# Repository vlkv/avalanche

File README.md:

# The Avalanche keyboard

The Avalanche keyboard is an ergonomic split keyboard with 4x6 (or 3x6 if you **break off the 'digits' row**) column staggered keys,
5 thumb keys, **1 additional key for the pinky** (break off-able too) and 2 additional keys for the index finger (64 keys total).

Avalanche design was inspired by a number of great keyboards. You may read more about it
in my very first [reddit post](https://www.reddit.com/r/MechanicalKeyboards/comments/mkwddp/introducing_the_avalanche_yet_another_one_ergo/).

Avalanche v4 (Awesome 40% and 60% builds by [u/chewiedies](https://www.reddit.com/user/chewiedies))

Avalanche v3

Avalanche v2

## Layout tester

Cut [left half](https://github.com/vlkv/avalanche/blob/master/layout_tester/pdf/Avalanche_v3_0_left_A4.pdf) and
[right half](https://github.com/vlkv/avalanche/blob/master/layout_tester/pdf/Avalanche_v3_0_right_A4.pdf)
from some piece of a cardboard, insert switches, put on the keycaps and try the layout.

## Gerber files

* [Version 4.2](https://github.com/vlkv/avalanche/tree/v4.2)
  * [PCB](https://github.com/vlkv/avalanche/blob/v4.2/pcb/Gerbers_pcb_v4_2.zip)
  * [Top plate](https://github.com/vlkv/avalanche/blob/v4.1/plate_top/Gerbers_plate_top_v4_1.zip)
  * [Bottom plate](https://github.com/vlkv/avalanche/blob/v4.1/plate_bottom/Gerbers_plate_bottom_v4_1.zip)
  * [60% 3D printed case](https://www.thingiverse.com/thing:5183389)
  * [40% 3D printed case](https://www.thingiverse.com/thing:5183613)
* [Version 3.1](https://github.com/vlkv/avalanche/tree/v3.1).
  * [PCB](https://github.com/vlkv/avalanche/blob/v3.1/pcb/Gerbers_pcb_v3_1.zip)
  * [Top plate](https://github.com/vlkv/avalanche/blob/v3.1/plate_top/Gerbers_plate_top_v3_0.zip)
  * [Bottom plate](https://github.com/vlkv/avalanche/blob/v3.1/plate_bottom/Gerbers_plate_bottom_v3_0.zip)
  * [Cover](https://github.com/vlkv/avalanche/blob/v3.1/cover/Gerbers_cover_v3_0.zip).
* [Version 3.0](https://github.com/vlkv/avalanche/tree/v3.0).
  * Known issues:
    * Still not fixed! https://github.com/vlkv/avalanche/issues/8
  * [PCB](https://github.com/vlkv/avalanche/blob/v3.0/pcb/Gerbers_pcb_v3_0.zip)
  * [Top plate](https://github.com/vlkv/avalanche/blob/v3.0/plate_top/Gerbers_plate_top_v3_0.zip)
  * [Bottom plate](https://github.com/vlkv/avalanche/blob/v3.0/plate_bottom/Gerbers_plate_bottom_v3_0.zip)
  * [Cover](https://github.com/vlkv/avalanche/blob/master/cover/Gerbers_cover_v3_0.zip). TODO: use git tag in this URI
* [Version 2.2](https://github.com/vlkv/avalanche/tree/v2.2).
  * Known issues:
    * Still not fixed! https://github.com/vlkv/avalanche/issues/8
  * [PCB](https://github.com/vlkv/avalanche/blob/v2.2/pcb/Gerbers_pcb.zip)
  * [Top plate](https://github.com/vlkv/avalanche/blob/v2.2/plate_top/Gerbers_plate_top.zip)
  * [Bottom plate](https://github.com/vlkv/avalanche/blob/v2.2/plate_bottom/Gerbers_plate_bottom.zip)
  * TODO: Add ProMicro/OLED cover gerber files...
* [Version 1.1](https://github.com/vlkv/avalanche/tree/v1.1).
  * [PCB](https://github.com/vlkv/avalanche/blob/v1.1/pcb/Gerbers_pcb.zip)
  * [Top plate](https://github.com/vlkv/avalanche/blob/v1.1/plate_top/Gerbers_plate_top.zip)
  * [Bottom plate](https://github.com/vlkv/avalanche/blob/v1.1/plate_bottom/Gerbers_plate_bottom.zip)

## Release notes
Are [here](https://github.com/vlkv/avalanche/blob/master/release_notes.md).

## Parts list
Is [here](https://github.com/vlkv/avalanche/blob/master/parts_list.md).

## Build instructions

Are [here](https://github.com/vlkv/avalanche/blob/master/build_instructions.md). These instructions are very brief
and insufficient as a detailed build instructions for a beginner. That is why (if you are a beginner) I recommend you
to also read these resourses:
* [ErgoTravel Build Instructions](https://github.com/jpconstantineau/ErgoTravel/blob/master/BuildInstructions.md)
* [Jian Build Instructons](https://telegra.ph/Gajd-po-sborke-Jian-12-08)
* [Joric wiki](https://github.com/joric/jorne/wiki)

## Chat group
There is a [chat group in Telegram](https://t.me/avalanche_kb), where you may chat about the project or ask some questions/help.

## Firmware

* [QMK](https://github.com/vlkv/qmk_firmware/tree/master/keyboards/avalanche).
* [ZMK from our friend romones](https://github.com/romones/zmk-config). According to him: "Keyboard works, encoders work. I couldn’t figure out lights and displays. And if you plan to use it note there is an override for a dead pin in right overlay".

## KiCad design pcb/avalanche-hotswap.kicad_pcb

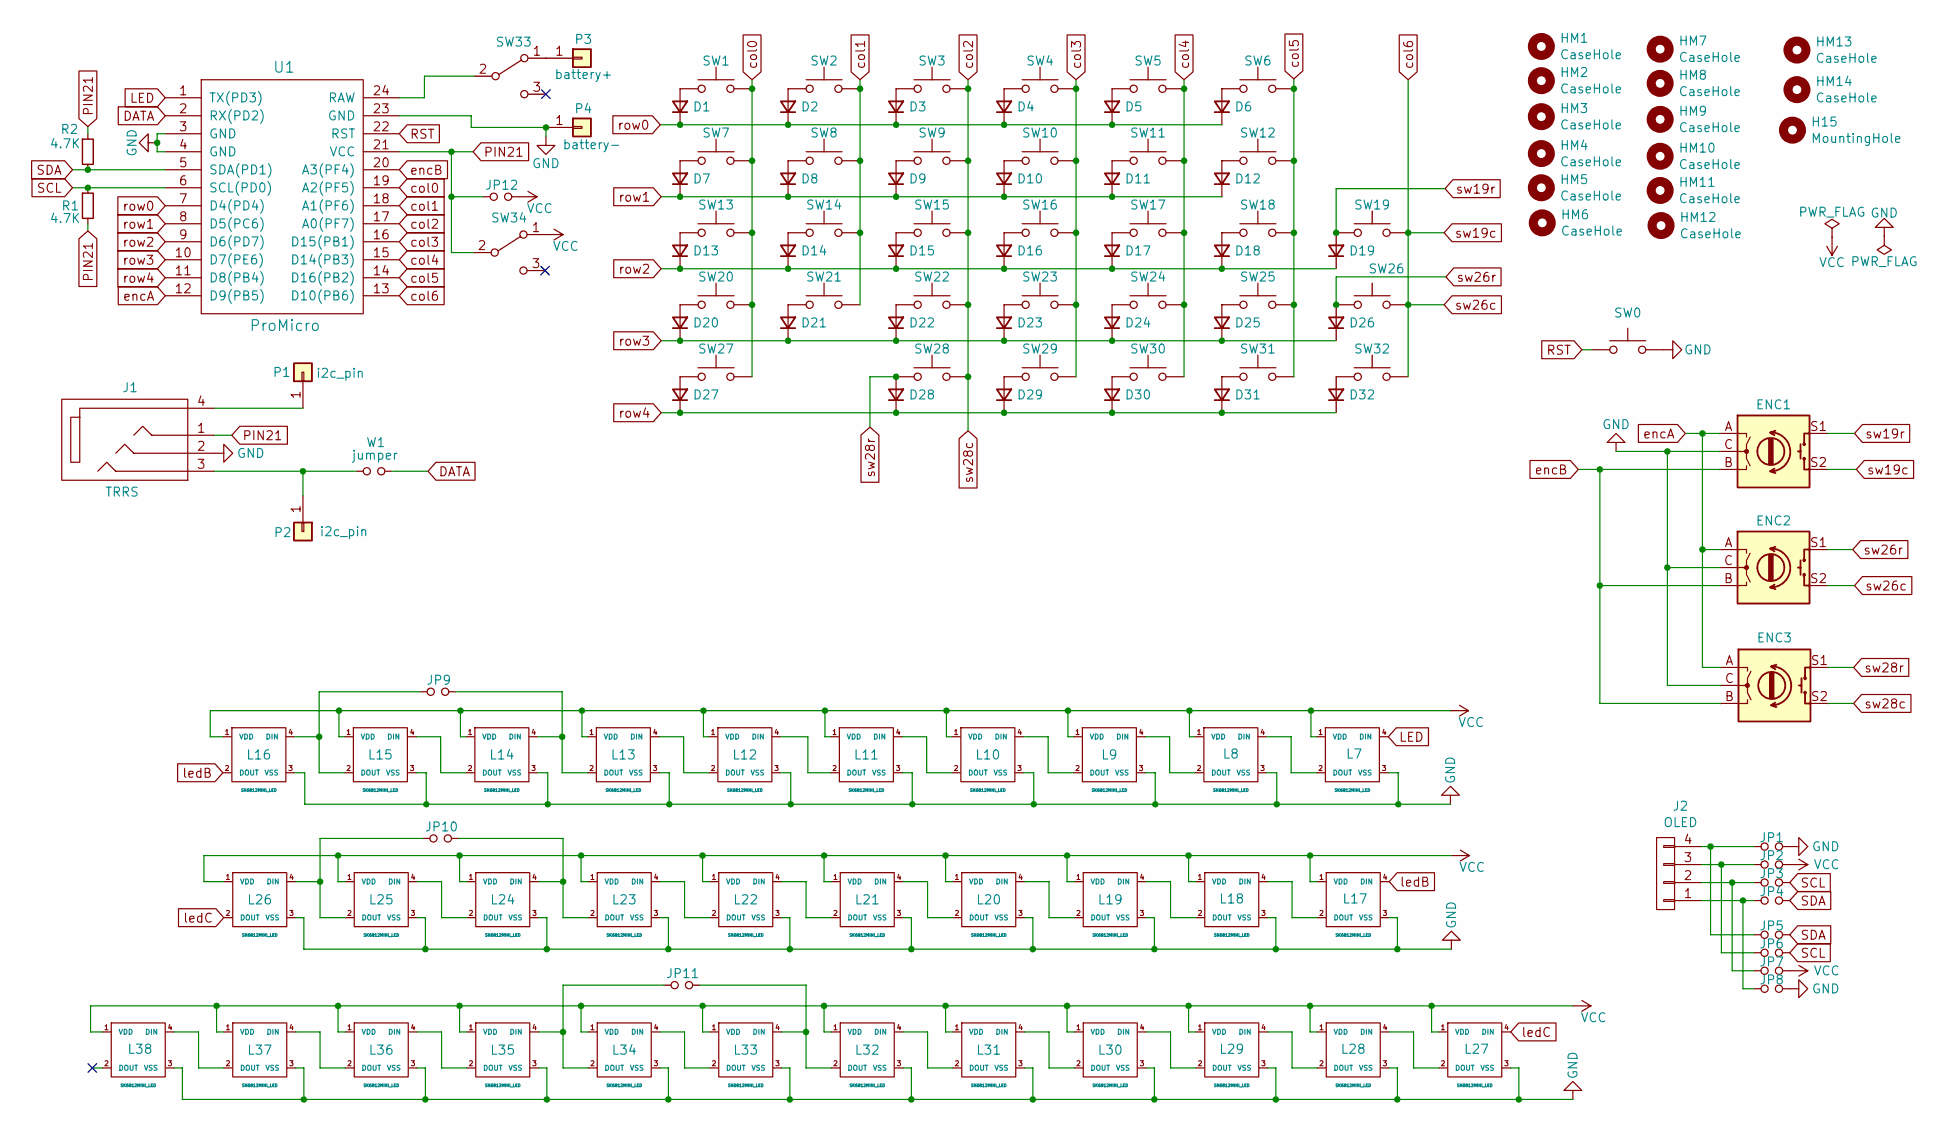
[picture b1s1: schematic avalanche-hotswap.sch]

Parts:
D1, D2, D3, D4, D5, D6, D7, D8, D9, D10, D11, D12, D13, D14, D15, D16, D17, D18, D19, D20, D21, D22, D23, D24, D25, D26, D27, D28, D29, D30, D31, D32: 1N4148; diode_TH_SMD
ENC1, ENC2, ENC3: Rotary_Encoder_Switch; RotaryEncoder_Alps_EC11E-Switch_Vertical_H20mm-keebio_modif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
H15: MountingHole; M2_HOLE_PCB
HM1, HM2, HM3, HM4, HM5, HM6, HM7, HM8, HM9, HM10, HM11, HM12, HM13, HM14: CaseHole; M2_HOLE_PCB
J1: TRRS; MJ-4PP-9
J2: OLED; OLED_4Pin_SSD1306
JP1, JP2, JP3, JP4, JP5, JP6, JP7, JP8, JP12: Device_Jumper_NO_Small; avalanche_Jumper
JP9, JP10, JP11: Device_Jumper_NO_Small; Jumper_rev
L7, L8, L9, L10, L11, L12, L13, L14, L15, L16, L17, L18, L19, L20, L21, L22, L23, L24, L25, L26, L27, L28, L29, L30, L31, L32, L33, L34, L35, L36, L37, L38: SK6812MINI_LED; YS-SK6812MINI-E
P1, P2: i2c_pin; 1pin_conn
P3: battery+; 1pin_conn
P4: battery-; 1pin_conn
R1, R2: 4.7K; Resistor_Hybrid_1205
SW0: SW_Push; Switch_Reset_THT
SW1, SW2, SW3, SW4, SW5, SW6, SW7, SW8, SW9, SW10, SW11, SW12, SW13, SW14, SW15, SW16, SW17, SW18, SW19, SW20, SW21, SW22, SW23, SW24, SW25, SW26, SW27, SW28, SW29, SW30, SW31, SW32: SW_Push; CherryMX_MidHeight_Hotswap_1u
SW33, SW34: SW_DPDT_x2; Switch_MSK-12C01-07
U1: ProMicro; ProMicro_rev2
W1: jumper; avalanche_Jumper

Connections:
DATA: U1.2 (RX(PD2)), W1.1
GND: ENC1.C, ENC2.C, ENC3.C, J1.2, JP1.2, JP8.2, L7.3 (VSS), L8.3 (VSS), L9.3 (VSS), L10.3 (VSS), L11.3 (VSS), L12.3 (VSS), L13.3 (VSS), L14.3 (VSS), L15.3 (VSS), L16.3 (VSS), L17.3 (VSS), L18.3 (VSS), L19.3 (VSS), L20.3 (VSS), L21.3 (VSS), L22.3 (VSS), L23.3 (VSS), L24.3 (VSS), L25.3 (VSS), L26.3 (VSS), L27.3 (VSS), L28.3 (VSS), L29.3 (VSS), L30.3 (VSS), L31.3 (VSS), L32.3 (VSS), L33.3 (VSS), L34.3 (VSS), L35.3 (VSS), L36.3 (VSS), L37.3 (VSS), L38.3 (VSS), P4.1, SW0.2, U1.3 (GND), U1.4 (GND), U1.23 (GND)
LED: L7.4 (DIN), U1.1 (TX(PD3))
unnamed: D1.2 (A), SW1.1
unnamed: D2.2 (A), SW2.1
unnamed: D3.2 (A), SW3.1
unnamed: D4.2 (A), SW4.1
unnamed: D5.2 (A), SW5.1
unnamed: D6.2 (A), SW6.1
unnamed: D7.2 (A), SW7.1
unnamed: D8.2 (A), SW8.1
unnamed: D9.2 (A), SW9.1
unnamed: D10.2 (A), SW10.1
unnamed: D11.2 (A), SW11.1
unnamed: D12.2 (A), SW12.1
unnamed: D13.2 (A), SW13.1
unnamed: D14.2 (A), SW14.1
unnamed: D15.2 (A), SW15.1
unnamed: D16.2 (A), SW16.1
unnamed: D17.2 (A), SW17.1
unnamed: D18.2 (A), SW18.1
unnamed: D20.2 (A), SW20.1
unnamed: D21.2 (A), SW21.1
unnamed: D22.2 (A), SW22.1
unnamed: D23.2 (A), SW23.1
unnamed: D24.2 (A), SW24.1
unnamed: D25.2 (A), SW25.1
unnamed: D27.2 (A), SW27.1
unnamed: D29.2 (A), SW29.1
unnamed: D30.2 (A), SW30.1
unnamed: D31.2 (A), SW31.1
unnamed: D32.2 (A), SW32.1
unnamed: J1.3, P2.1, W1.2
unnamed: J1.4, P1.1
unnamed: J2.1, JP4.1, JP8.1
unnamed: J2.2, JP3.1, JP7.1
unnamed: J2.3, JP2.1, JP6.1
unnamed: J2.4, JP1.1, JP5.1
unnamed: JP9.1, L15.2 (DOUT), L16.4 (DIN)
unnamed: JP9.2, L13.2 (DOUT), L14.4 (DIN)
unnamed: JP10.1, L25.2 (DOUT), L26.4 (DIN)
unnamed: JP10.2, L23.2 (DOUT), L24.4 (DIN)
unnamed: JP11.1, L34.2 (DOUT), L35.4 (DIN)
unnamed: JP11.2, L32.2 (DOUT), L33.4 (DIN)
unnamed: L7.2 (DOUT), L8.4 (DIN)
unnamed: L8.2 (DOUT), L9.4 (DIN)
unnamed: L10.2 (DOUT), L11.4 (DIN)
unnamed: L9.2 (DOUT), L10.4 (DIN)
unnamed: L11.2 (DOUT), L12.4 (DIN)
unnamed: L12.2 (DOUT), L13.4 (DIN)
unnamed: L14.2 (DOUT), L15.4 (DIN)
unnamed: L17.2 (DOUT), L18.4 (DIN)
unnamed: L18.2 (DOUT), L19.4 (DIN)
unnamed: L19.2 (DOUT), L20.4 (DIN)
unnamed: L20.2 (DOUT), L21.4 (DIN)
unnamed: L21.2 (DOUT), L22.4 (DIN)
unnamed: L22.2 (DOUT), L23.4 (DIN)
unnamed: L24.2 (DOUT), L25.4 (DIN)
unnamed: L27.2 (DOUT), L28.4 (DIN)
unnamed: L28.2 (DOUT), L29.4 (DIN)
unnamed: L29.2 (DOUT), L30.4 (DIN)
unnamed: L30.2 (DOUT), L31.4 (DIN)
unnamed: L31.2 (DOUT), L32.4 (DIN)
unnamed: L33.2 (DOUT), L34.4 (DIN)
unnamed: L35.2 (DOUT), L36.4 (DIN)
unnamed: L36.2 (DOUT), L37.4 (DIN)
unnamed: L37.2 (DOUT), L38.4 (DIN)
unnamed: P3.1, SW33.1 (A)
unnamed: SW33.2 (B), U1.24 (RAW)
PIN21: J1.1, JP12.1, R1.2, R2.1, SW34.2 (B), U1.21 (VCC)
RST: SW0.1, U1.22 (RST)
SCL: JP3.2, JP6.2, R1.1, U1.6 (SCL(PD0))
SDA: JP4.2, JP5.2, R2.2, U1.5 (SDA(PD1))
VCC: JP2.2, JP7.2, JP12.2, L7.1 (VDD), L8.1 (VDD), L9.1 (VDD), L10.1 (VDD), L11.1 (VDD), L12.1 (VDD), L13.1 (VDD), L14.1 (VDD), L15.1 (VDD), L16.1 (VDD), L17.1 (VDD), L18.1 (VDD), L19.1 (VDD), L20.1 (VDD), L21.1 (VDD), L22.1 (VDD), L23.1 (VDD), L24.1 (VDD), L25.1 (VDD), L26.1 (VDD), L27.1 (VDD), L28.1 (VDD), L29.1 (VDD), L30.1 (VDD), L31.1 (VDD), L32.1 (VDD), L33.1 (VDD), L34.1 (VDD), L35.1 (VDD), L36.1 (VDD), L37.1 (VDD), L38.1 (VDD), SW34.1 (A)
col0: SW1.2, SW7.2, SW13.2, SW20.2, SW27.2, U1.19 (A2(PF5))
col1: SW2.2, SW8.2, SW14.2, SW21.2, U1.18 (A1(PF6))
col2: ENC3.S2, SW3.2, SW9.2, SW15.2, SW22.2, SW28.2, U1.17 (A0(PF7))
col3: SW4.2, SW10.2, SW16.2, SW23.2, SW29.2, U1.16 (D15(PB1))
col4: SW5.2, SW11.2, SW17.2, SW24.2, SW30.2, U1.15 (D14(PB3))
col5: SW6.2, SW12.2, SW18.2, SW25.2, SW31.2, U1.14 (D16(PB2))
col6: ENC1.S2, ENC2.S2, SW19.2, SW26.2, SW32.2, U1.13 (D10(PB6))
encA: ENC1.A, ENC2.A, ENC3.A, U1.12 (D9(PB5))
encB: ENC1.B, ENC2.B, ENC3.B, U1.20 (A3(PF4))
ledB: L16.2 (DOUT), L17.4 (DIN)
ledC: L26.2 (DOUT), L27.4 (DIN)
row0: D1.1 (K), D2.1 (K), D3.1 (K), D4.1 (K), D5.1 (K), D6.1 (K), U1.7 (D4(PD4))
row1: D7.1 (K), D8.1 (K), D9.1 (K), D10.1 (K), D11.1 (K), D12.1 (K), U1.8 (D5(PC6))
row2: D13.1 (K), D14.1 (K), D15.1 (K), D16.1 (K), D17.1 (K), D18.1 (K), D19.1 (K), U1.9 (D6(PD7))
row3: D20.1 (K), D21.1 (K), D22.1 (K), D23.1 (K), D24.1 (K), D25.1 (K), D26.1 (K), U1.10 (D7(PE6))
row4: D27.1 (K), D28.1 (K), D29.1 (K), D30.1 (K), D31.1 (K), D32.1 (K), U1.11 (D8(PB4))
sw19r: D19.2 (A), ENC1.S1, SW19.1
sw26r: D26.2 (A), ENC2.S1, SW26.1
sw28r: D28.2 (A), ENC3.S1, SW28.1

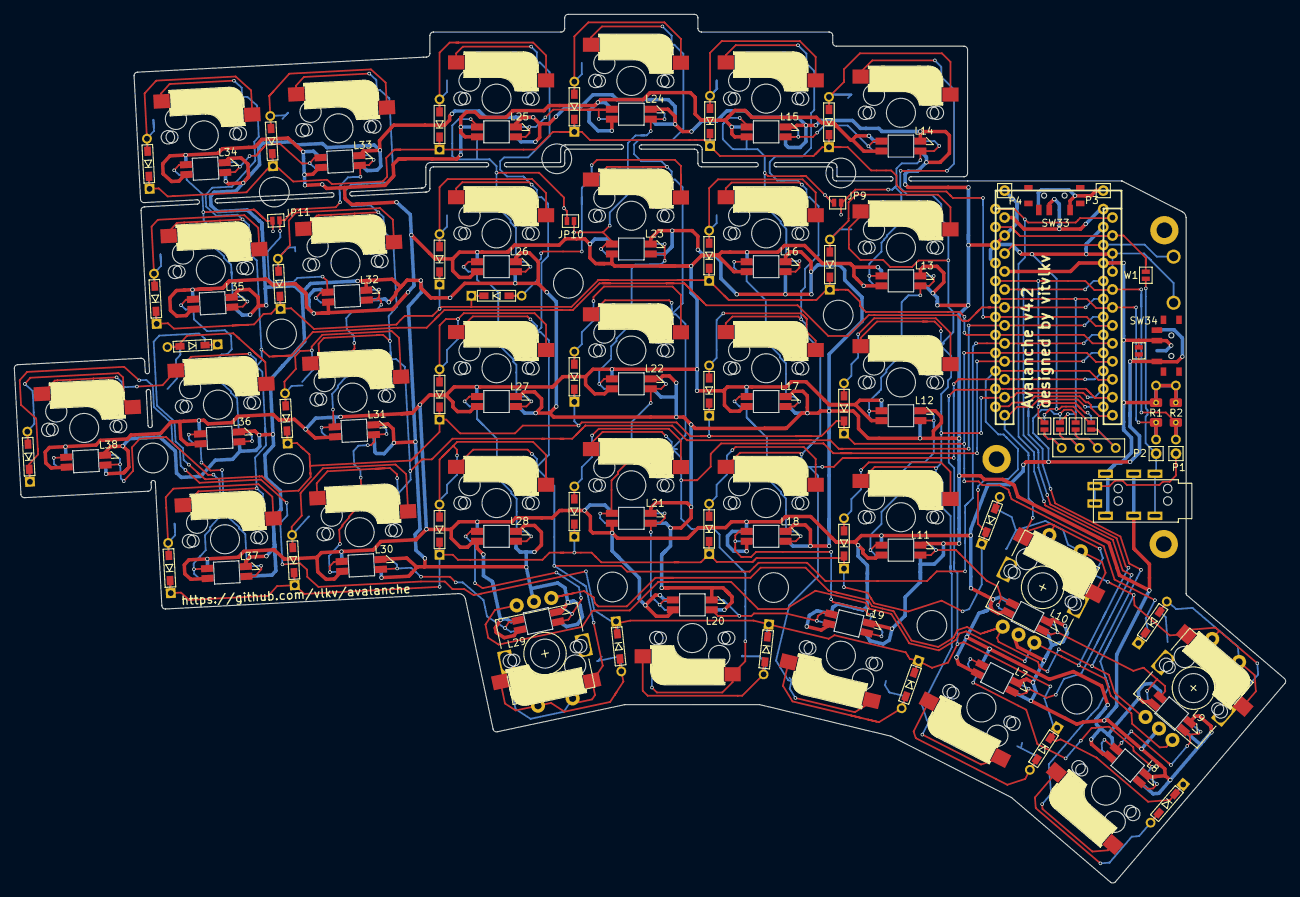
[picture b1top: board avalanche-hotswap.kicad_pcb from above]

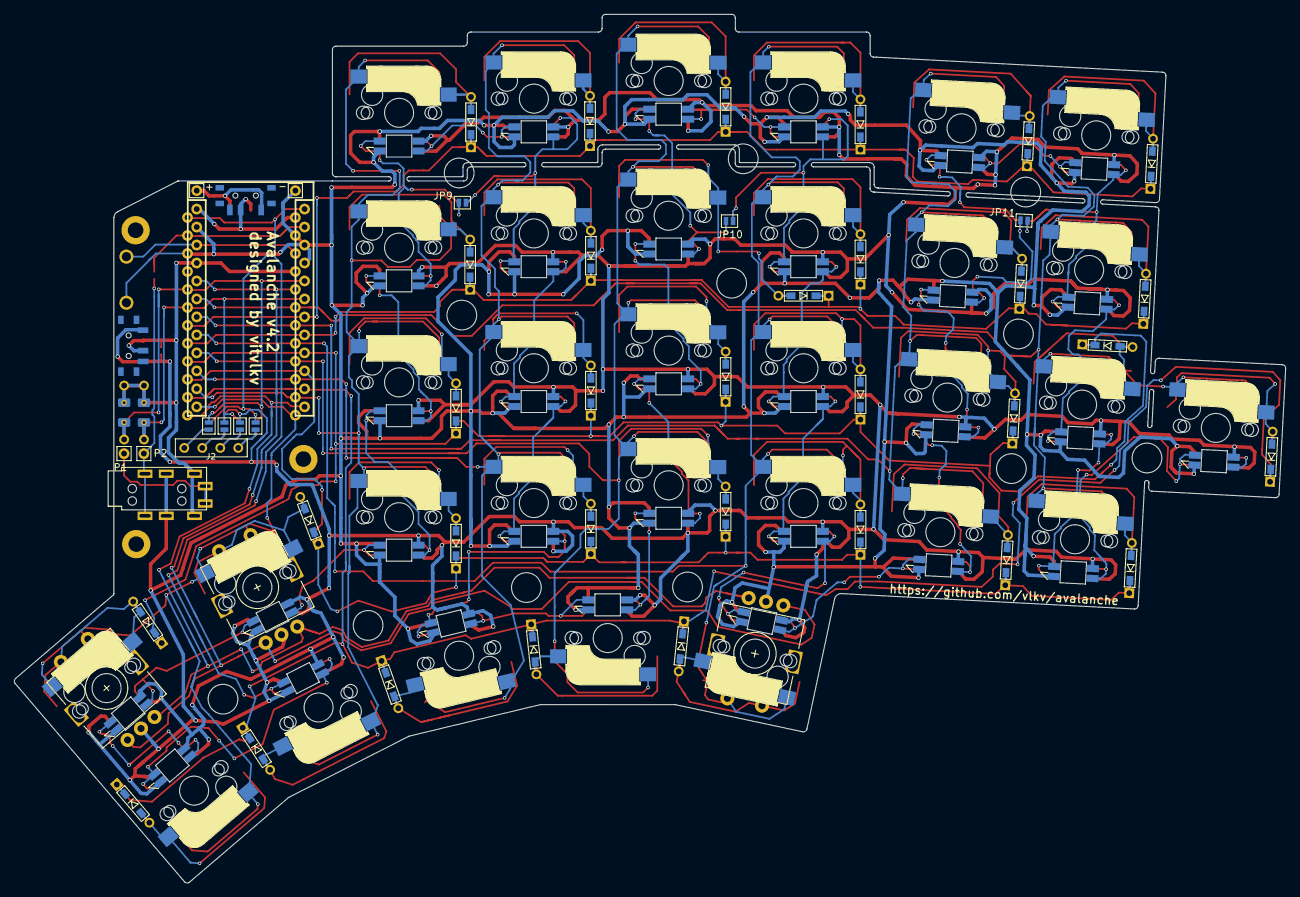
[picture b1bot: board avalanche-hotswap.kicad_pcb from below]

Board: 2 copper layers, 179.7 x 122.7 mm, 139 parts (5 on the bottom side), 93 nets.

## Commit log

2021-02-25 Initial commit with my current pcb project "Thing60"
2021-02-26 Work in progress
2021-02-26 Added new footprints
2021-02-26 Lined everything up to grid 0.05mm
2021-02-26 Positioned rows and cols
2021-02-26 Roughly cut edges, fixed footprints on the scheme.
2021-02-26 Rounded some edges.
2021-02-27 Cuts 1mm width
2021-02-27 Rotated thumb switches to 180 degrees.
2021-02-27 Routing...
2021-02-27 All routes seems to be connected.
2021-02-28 Moved diode a bit
2021-02-28 Aligned everything to 0.05 grid.
2021-02-28 Aligned cut to 0.05 grid.
2021-02-28 Modified ProMicro footprint making it a dual
2021-02-28 Routing dual ProMicro footprint
2021-02-28 Routing dual ProMicro footprint. Done.
2021-02-28 Fixed ProMicro footprint silk layer
2021-02-28 Updated fotprint on the scheme
2021-03-02 Started new simple and weird design.
2021-03-02 Routing is done.
2021-03-02 Readme update
2021-03-02 Holes.
2021-03-03 Curved cut.
2021-03-03 Re-routing.
2021-03-03 Top Plate
2021-03-03 Bottom plate draft
2021-03-03 Holes
2021-03-03 Cuts
2021-03-03 Edges cuts
2021-03-03 Added filled areas.
2021-03-04 Renamed emu to avalanche
2021-03-04 Renamed images
2021-03-04 Removed emu files
2021-03-04 Added text to the PCB
2021-03-05 Added to schema: * OLED * LED
    Imported some footprints and symbols from Lily58
2021-03-05 Moved all symbols to avalanche-hotswap.lib
2021-03-05 Added underglow LEDs and many more...
2021-03-06 Routing LEDs
2021-03-07 Moving diodes.
2021-03-07 Renumbered switches and diodes.
2021-03-07 Added one more underglow LED
2021-03-08 Prepared to route the promicro
2021-03-08 Routing the promicro...
2021-03-08 Added GND filled zones.
2021-03-08 Netlist is connected.
2021-03-08 Added doc
2021-03-08 Fixed cut edges + filled zones on plates.
2021-03-08 Using different cutout footprints
2021-03-08 Using different M2 holes.
2021-03-08 Added dimensions.
2021-03-08 Changed schema
2021-03-08 Minor improvements for holes.
2021-03-08 Created gerber files.
2021-03-08 Reduced width of the top plate for 0.05mm
2021-03-08 Regenerated Gerbers for top plate
2021-03-08 Renamed zips
2021-03-08 Changed layer from silk to comments
2021-03-08 Added User Drawings layer to gerbers
2021-03-10 Added an image
2021-03-10 Fixed path to image
2021-03-10 Images 62, 50 and 48 variants.
2021-04-05 New image
2021-04-06 Created project for cover plate
2021-04-06 One more image of the board
2021-04-07 Creating layout tester
2021-04-07 Printed layout tester to PDF
2021-04-07 Moved images to avalanche_info
2021-04-07 - Moved SW13 to a different row and col (needed to free one ProMicro pin) - Added rotary encoders to the scheme - Added rotary encoders footprint
2021-04-07 Rerouted SW13
2021-04-07 - Added encoders to their place. Not routed yet. - Moved one case hole. Both on pcb and bottom-plate.
2021-04-08 Layout tester improve
2021-04-08 Routed all three encoders
2021-04-08 Routed
2021-04-08 Moved case hole more downwards
2021-04-08 moved reset button a bit down
2021-04-08 Changed LEDs to WS2812B
2021-04-08 Updated version label. Moved OLED connections a bit down.
2021-04-10 Started replacing diodes footprints (SMD only).
2021-04-10 WIP on smd diodes...
2021-04-10 WIP on diodes. Moved a case hole a little bit
2021-04-10 WIP on diodes...
2021-04-10 WIP on diodes. Almost done.
2021-04-11 Added per-switch LEDs (not routed yet).
2021-04-11 WIP on LEDs
2021-04-11 Rotated SW27 to 180 degrees angle.
2021-04-11 Routing encoder after rotate. Moved case hole a little.
2021-04-11 WIP routing LEDs...
2021-04-12 WIP routing LEDs (done with "LED" track)
2021-04-13 WIP routing the ground
2021-04-13 Added jumpers for LEDs in case of nums row break-off
2021-04-15 Routed the ground
2021-04-15 Fixed ground routing
2021-04-15 Routed LED jumpers
2021-04-15 Swapped LED 36 and 37 to fix break-offability of the pinky key.
2021-04-15 Rotated 90 degrees D14
2021-04-17 Moved diodes a little bit away from rotary encoders
2021-04-17 Removed filled zones (ground)
2021-04-17 Removed unused footprints
2021-04-17 Using new Jumper_rev footprint
2021-04-17 Fixed problem with a monting hole. Moved P1 and P2 up (closer to the resistors)
2021-04-17 Moved OLED
2021-04-17 Added labels for jumpers
2021-04-17 Added labels for background LEDs pads
2021-04-18 Minor fix of the via
2021-04-18 Replaced diode footprints with smd+th
2021-04-18 Minor fixes in diodes
2021-04-18 Still moving diodes
2021-04-19 Moving diodes
2021-04-19 Rotated resistors
2021-04-19 Done with moving resistors
2021-04-22 Fixed LED footprints
2021-04-22 Updated other schemes
2021-04-22 Fixed LED symbol
2021-04-22 Fixed scheme and netlist
2021-04-22 Updated footprints
2021-04-22 Cleaned up tracks and vias
2021-04-22 Rerouted bg LEDs
2021-04-22 Routing LEDs...
2021-04-22 Minor fix
2021-04-23 Changed the shape of the right edge.
2021-04-24 Routing LEDs is done.
2021-04-24 Moving thumb cluster to the right a bit... WIP
2021-04-24 Moving the thumb cluster WIP...
2021-04-25 Rerouted tracks after the thumb cluster move.
2021-04-25 Moved trrs closer to the promicro
2021-04-25 Working on a new design for the top plate.
2021-04-25 Routed RESET in its new location.
2021-04-25 Multiple fixes...
2021-04-28 Rotated 4.5 degrees three leftmost columns
2021-04-28 Moved thumb cluster + index buttons
2021-04-28 New egde cuts
2021-04-29 Routing is generally done.
2021-04-29 Added one more button!
2021-04-29 Renumbered switches
2021-04-29 Renumbered LEDs
2021-04-29 Added dimensions
2021-04-29 Deleted extra tracks & vias
2021-04-29 top + bottom plates
2021-04-29 Minor changes
2021-04-29 Layout tester
2021-04-30 Moved diode
2021-04-30 Rotated LED
2021-04-30 Changed holes a bit. Removed old gerbers.
2021-04-30 Cleaned up tracks and vias + minor change.
2021-04-30 Corrected a label
2021-04-30 Generated gerbers for the Avalanche 2.0
2021-04-30 Removed copper layers from top and bottom plates
2021-05-21 Fixed TRRS connector position
2021-05-21 Changed resistor's footprint (to support TH resistors)
2021-05-21 Changed the version on label
2021-05-21 Fixed GND routing
2021-05-21 Generated pcb gerbers for v1.1
2021-06-08 Added files from avalanche-info
2021-06-08 Working on the docs
2021-06-08 Fixed texts
2021-06-08 Parts list
2021-06-08 Minor change
2021-06-08 Added URL about the chat
2021-06-08 Parts list in a separate file
2021-06-08 Rotated R1. Updated the label with version on silk layer
2021-06-08 Version 2.1
2021-06-08 Added license
2021-06-08 Bold text
2021-07-02 Removed SW19 (and related)
2021-07-02 Moved SW26
2021-07-02 Working on thumb cluster
2021-07-03 Reverted the sch and netlist (Returned back SW19)
2021-07-03 Updated pcb design to the sch
2021-07-03 Routing
2021-07-04 Routing is generally done
2021-07-04 Mounting holes
2021-07-04 Plates
2021-07-04 Made mounting holes big
2021-07-04 Moved two mounting holes a bit
2021-07-04 Moved OLEDs a bit down
2021-07-05 Added MKS switches
2021-07-05 Moving holes
2021-07-05 Connected OLED after switch. Moved trrs.
2021-07-05 Fixed location of two buttons in thumb cluster
2021-07-05 Multiple fixes
2021-07-05 Added reset label
2021-07-05 Renamed old gerber zips
2021-07-05 Cleaned up track and vias
2021-07-05 Moved diodes
2021-07-05 Generated gerber files
2021-07-08 Updated the layout tester
2021-07-26 Fixed the footprint #8
2021-08-01 Disconnected all the per-key LEDs
2021-08-01 Rerouting...
2021-08-01 Done with #8
2021-08-01 Fixed #9 (Problems after breaking-off the numbers row)
2021-08-01 Created Gerbers of v2.2
2021-09-03 Added v3 image
2021-09-03 Fixed urls
2021-09-03 Added issues
2021-09-03 Fixed standoffs in the parts list
2021-09-03 Urls
2021-09-03 Created cover
2021-09-03 Fixed uri
2021-09-03 Typo fix
2021-09-03 Deleted tracks around per-key LEDs
2021-09-03 Updated all the LED footprints on the pcb
2021-09-08 Rerouting of LEDs is done!
2021-09-08 Moved OLED up
2021-09-08 Plot the PCB gerbers
2021-09-09 Replaced image
2021-09-09 Url fix
2021-10-16 Removed background LEDs
2021-10-16 Reduced the angle of "pinky stagger" for 1.5 degrees
2021-10-17 Removed OLEDs
2021-10-18 Moved things around...
2021-10-18 Added wide horizontal OLED SSD1306
2021-10-18 Rerouting
2021-10-18 Changing stagger
2021-10-18 Working on stagger
2021-10-18 Stagger is done
2021-10-18 Moved thumb cluster up+left a bit
2021-10-19 Holes and top plate
2021-10-19 More minor changes
2021-10-19 Generated gerbers for v4.0
2021-10-19 Fixed edges
2021-10-20 Working on edges
2021-10-21 Edge cuts
2021-10-21 Moved promicro up a bit
2021-10-21 Routing is fixed
2021-10-21 WIP on the top plate
2021-10-22 Bottom plate
2021-10-22 Final fixes for v4.1
2021-10-22 Gerbers for v4.1
2021-11-05 Top and bottom plates v4.0
2021-11-05 Gerbers for top and bottom plates v4.0
2021-11-27 Added image of ava v4
2021-11-27 Added an url
2021-11-27 Updated release notes and parts list
2021-11-30 Created the promicro cover
2021-11-30 Created a top cover for v4.0
2021-11-30 Top cover gerbers
2021-12-04 Added info about the issue
2021-12-10 Fixed GND shortened to RST in Avalanche 4.0 and 4.1 #10
2021-12-10 Change the OLED pins order in Avalanche 4.0 and 4.1 #11
2021-12-10 Changed the version to 4.2 on the silkscreen
2021-12-10 New version
2021-12-10 Deleted buggy versions
2022-01-03 added urls to cases
2022-02-21 Clarify build documentation and add communication wiring diagram.
2022-02-24 Update documentation to include micro switch.
2022-02-26 Add comments for LEDs.
2022-02-28 Added a jumper for connecting SW34.
2022-08-25 Added url for ZMK
